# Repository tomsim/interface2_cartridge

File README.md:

# Game Cartridge for ZX Spectrum

A clon as similar as posible to the original 16K Rom game cartridges.

Aditional capabilities (for writting on chip after solder, to select between 8 games, etc...

And a similar PCB to use with the Dandanator mini 2.0 VC interface, that use 512K, you can use for Sword of Ianna, Castelvania, Mighty Final Fight, La abadia del crimen and a lot more games.

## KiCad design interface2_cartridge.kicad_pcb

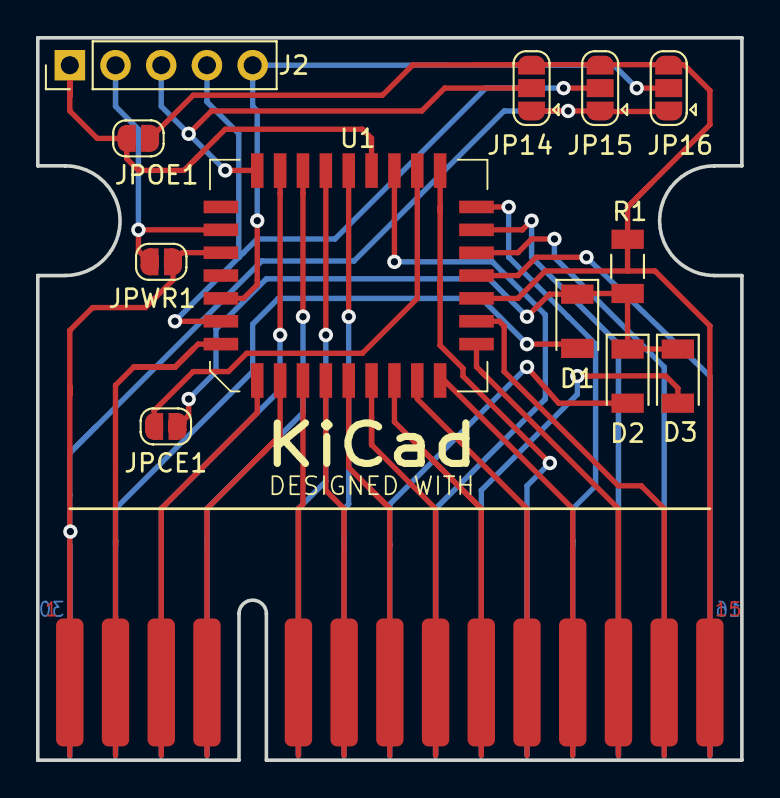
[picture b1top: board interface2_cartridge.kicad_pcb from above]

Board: 2 copper layers, 39.1 x 40.1 mm, 13 parts (0 on the bottom side), 34 nets.

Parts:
D1, D2, D3: 1N4148; D_1206_3216Metric
J1: cartridge_IF2; CART_IF2_EDGE
J2: Conn_01x05; PinHeader_1x05_P2.54mm_Vertical
JP14, JP15, JP16: S; SolderJumper-3_P1.3mm_Open_RoundedPad1.0x1.5mm
JPCE1: CE; SolderJumper-2_P1.3mm_Open_RoundedPad1.0x1.5mm
JPOE1: OE; SolderJumper-2_P1.3mm_Open_RoundedPad1.0x1.5mm
JPWR1: WE; SolderJumper-2_P1.3mm_Open_RoundedPad1.0x1.5mm
R1: R; R_1206_3216Metric
U1: AM29F010B; PLCC-32

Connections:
+5V: J1.1, J1.2, JP14.1, JP15.1, JP16.1, JPWR1.1, U1.32
A0: J1.19, U1.12
A1: J1.17, U1.11
A2: J1.15, U1.10
A3: J1.13, U1.9
A4: J1.11, U1.8
A5: J1.9, U1.7
A6: J1.7, U1.6
A7: J1.5, U1.5
A8: J1.8, U1.27
A9: J1.10, U1.26
A10: J1.16, U1.23
A11: J1.12, U1.25
A12: J1.3, U1.4
A13: J1.6, U1.28
A14: J2.3, JP14.2, U1.29
A15: J2.4, JP15.2, U1.3
A16: J2.5, JP16.2, U1.2
D0: J1.21, U1.13
D1: J1.23, U1.14
D2: J1.25, U1.15
D3: J1.28, U1.17
D4: J1.26, U1.18
D5: J1.24, U1.19
D6: J1.22, U1.20
D7: J1.20, U1.21
GND: J1.27, JP14.3, JP15.3, JP16.3, JPOE1.2, R1.2, U1.16
unnamed: D1.1, D2.1, D3.1, JPCE1.2, R1.1
unnamed: D1.2, J1.4
unnamed: D2.2, J1.14
unnamed: D3.2, J1.18
unnamed: J2.1, JPOE1.1, U1.24
unnamed: J2.2, JPWR1.2, U1.31
unnamed: JPCE1.1, U1.22

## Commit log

2018-06-12 initial
2018-08-03 final design
2018-08-03 new card
2018-08-20 panelizados

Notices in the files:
interface2_cartridge.kicad_pcb:
(C) 2018 Alvaro Alea
